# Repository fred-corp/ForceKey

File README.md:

# Force Key

## Description

The Force Key solid-state morse paddle key, which, as the name implies, uses force senors (load cells) to detect the user's input. It is designed to work in single-lever mode or twin-lever mode.  
The output is a standard 3.5mm stereo jack, which can be connected to any morse keyer or transceiver.

## Features

- Single-lever or twin-lever mode, or both at the same time
- Adjustable sensitivity in code
- TRS 3.5mm stereo jack output (tip = dot, ring = dash, sleeve = ground)
- Li-Ion battery powered
- USB-C port for charging
- Uses cheap Puya microcontroller

## Hardware

- PCB & other components in BOM
- 2x [100g load cells + HX711 amplifier](https://fr.aliexpress.com/item/1005001537354199.html) (make sure to get the 100g version !)
- TODO: add more details

The HX711 has to be modded to output data at 80Hz rate, which is done by lifting pin 15 and bridging it to pin 16 :  

## Inspiration

The Force key is inspired by the [Solid State Paddle by 9A5N](https://www.9a5n.eu/paddle.html), which is a beautiful product; but because of my student budget, I decided to make my own version.  
It was a nice challenge as I wanted to use the Puya PY32F002A microcontroller, which is not very common in the maker community.  
I also wanted to machine the base and load cell supports myself, which was exciting as I don't get to use the mills and lathes of my university very often as I'm an EE student.

Please consider buying the original product if you can afford it, it's a great product and it's worth the price (thanks [F4IEY](https://github.com/f4iey) for showing it to me in the first place !).

## Pictures

### 3D Render from Autodesk Fusion

### Base machining

The final base ended up being 90x85x20mm due to the available scrap blank; the CAD was then adapted to fit the new dimensions.

It was amazing to be able to use the machines of my university. It took a whole afternoon to machine both parts (base and load-cell support), but it was really fun ! Thanks again to my teacher for all the help and advice.

### Base bluing

Before :  

After :  

After a lot of sanding with 180 and 320 scotch-brite, I used a cold bluing solution to give the base a nice black finish. It's not perfect nor uniform, but it gives a great old-school look to the base.

### Assembly

Partial assembly before bluing :  

Assembly before bluing :  

Partial assembly after bluing :

Final assembly :

## License & Acknowledgements

Made with ❤️, lots of ☕️, and lack of 🛌  
Published under CreativeCommons BY-SA 4.0

This work is licensed under a [Creative Commons Attribution-ShareAlike 4.0 International License](http://creativecommons.org/licenses/by-sa/4.0/).

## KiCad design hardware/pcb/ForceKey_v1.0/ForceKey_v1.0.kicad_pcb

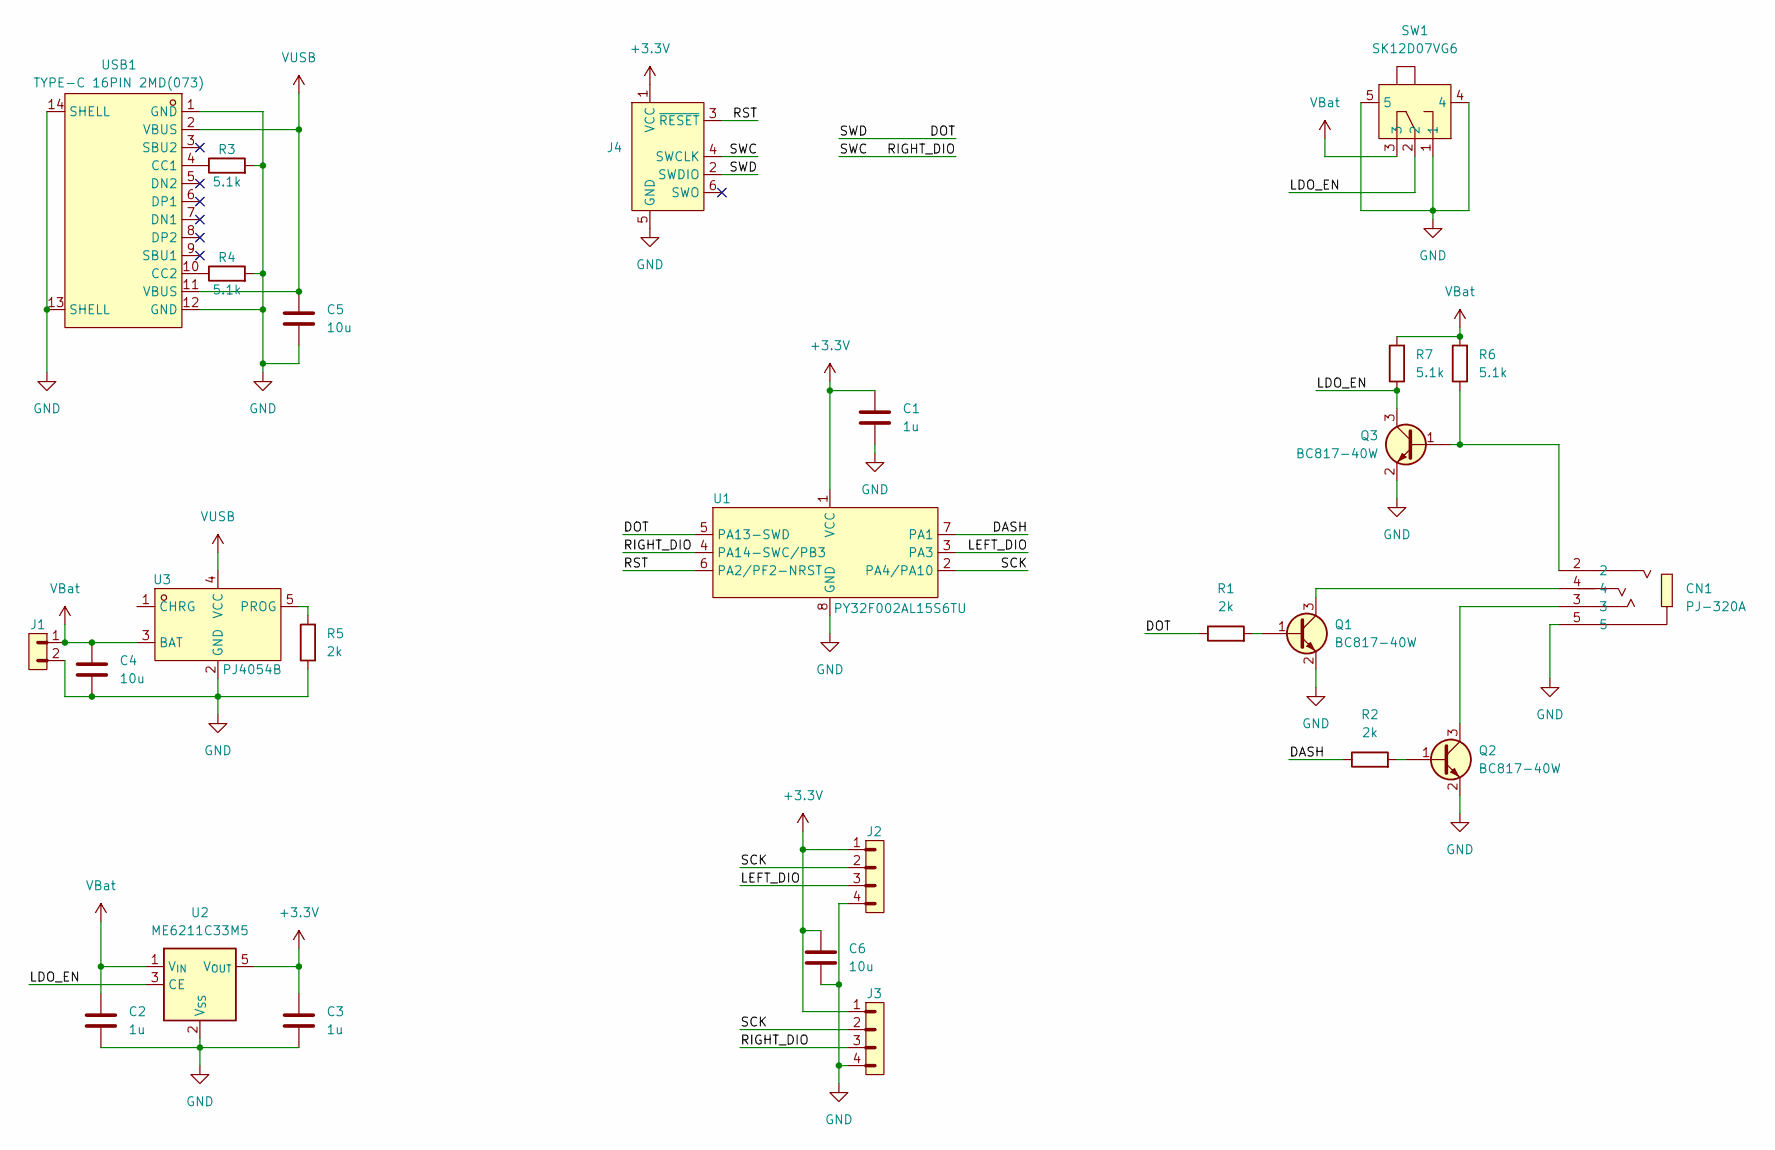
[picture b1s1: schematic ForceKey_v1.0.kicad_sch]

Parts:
C1, C2, C3: 1u; C_0603_1608Metric_Pad1.08x0.95mm_HandSolder
C4, C5, C6: 10u; C_0603_1608Metric_Pad1.08x0.95mm_HandSolder
CN1: PJ-320A; AUDIO-TH_XKB_PJ-320A; LCSC Part C2884926
J1: PINHD_1x2_Male; PinHeader_1x02_P2.54mm_Vertical
J2, J3: PINHD_1x4_Male; PinHeader_1x04_P2.54mm_Vertical
J4: Conn_ARM_SWD_TagConnect_TC2030-NL; Tag-Connect_TC2030-IDC-NL_2x03_P1.27mm_Vertical
Q1, Q2, Q3: BC817-40W; SOT-323_SC-70_Handsoldering
R1, R2, R5: 2k; R_0603_1608Metric_Pad0.98x0.95mm_HandSolder
R3, R4, R6, R7: 5.1k; R_0603_1608Metric_Pad0.98x0.95mm_HandSolder
SW1: SK12D07VG6; SW-TH_SK12D07VG6; LCSC Part C7272161
U1: PY32F002AL15S6TU; SOP-8_L4.9-W3.9-P1.27-LS6.0-BL-1; LCSC Part C5292060
U2: ME6211C33M5; SOT-23-5
U3: PJ4054B; SOT-23-5_L2.9-W1.6-P0.95-LS2.8-BL; LCSC Part C2911335
USB1: TYPE-C 16PIN 2MD(073); USB-C-SMD_TYPE-C-6PIN-2MD-073; LCSC Part C2765186

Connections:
+3.3V: C1.1, C3.1, C6.1, J2.1, J3.1, J4.1 (VCC), U1.1 (VCC), U2.5 (V_{OUT})
/DASH: R2.1, U1.7 (PA1)
/DOT: J4.2 (SWDIO), R1.1, U1.5 (PA13-SWD)
/LDO_EN: Q3.3 (C), R7.1, SW1.2, U2.3 (CE)
/LEFT_DIO: J2.3, U1.3 (PA3)
/RIGHT_DIO: J3.3, J4.4 (SWCLK), U1.4 (PA14-SWC/PB3)
/RST: J4.3 (~RESET), U1.6 (PA2/PF2-NRST)
/SCK: J2.2, J3.2, U1.2 (PA4/PA10)
GND: C1.2, C2.2, C3.2, C4.2, C5.2, C6.2, CN1.5, J1.2, J2.4, J3.4, J4.5 (GND), Q1.2 (E), Q2.2 (E), Q3.2 (E), R3.2, R4.2, R5.1, SW1.1, SW1.4, SW1.5, U1.8 (GND), U2.2 (V_{SS}), U3.2 (GND), USB1.1 (GND), USB1.12 (GND), USB1.13 (SHELL), USB1.14 (SHELL); also elsewhere on the board
unnamed: Q1.1 (B), R1.2
unnamed: CN1.4, Q1.3 (C)
unnamed: Q2.1 (B), R2.2
unnamed: CN1.3, Q2.3 (C)
unnamed: CN1.2, Q3.1 (B), R6.1
unnamed: R5.2, U3.5 (PROG)
unnamed: R3.1, USB1.4 (CC1)
unnamed: R4.1, USB1.10 (CC2)
VBat: C2.1, C4.1, J1.1, R6.2, R7.2, SW1.3, U2.1 (V_{IN}), U3.3 (BAT)
VUSB: C5.1, U3.4 (VCC), USB1.2 (VBUS), USB1.11 (VBUS)

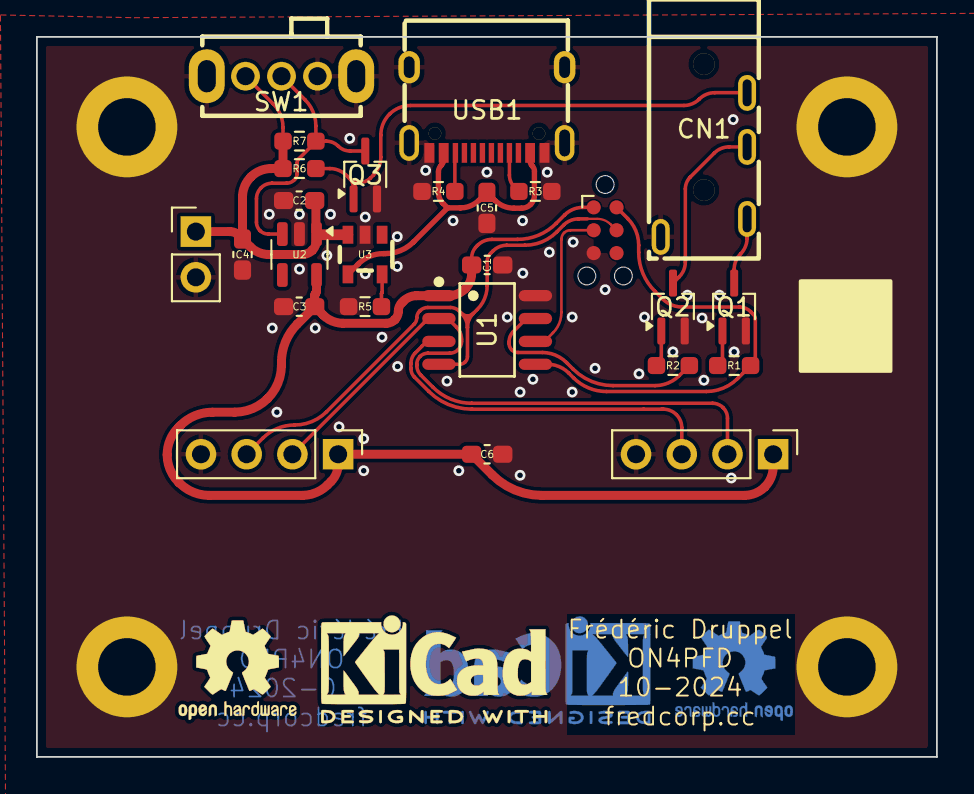
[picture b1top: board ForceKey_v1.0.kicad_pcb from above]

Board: 2 copper layers, 50.0 x 40.0 mm, 30 parts (0 on the bottom side), 19 nets.

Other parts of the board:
H1, H2, H3, H4: MountingHole_3.2mm_M3_DIN965_Pad

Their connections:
GND: H1.1, H2.1, H3.1, H4.1; also elsewhere on the board

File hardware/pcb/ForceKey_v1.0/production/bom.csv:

Designator,Footprint,Quantity,Value,LCSC Part #
"C1, C2, C3",0603,3,1u,
"C4, C5, C6",0603,3,10u,
CN1,AUDIO-TH_XKB_PJ-320A,1,PJ-320A,C2884926
J1,PinHeader_1x02_P2.54mm_Vertical,1,PINHD_1x2_Male,
"J2, J3",PinHeader_1x04_P2.54mm_Vertical,2,PINHD_1x4_Male,
"Q1, Q2, Q3",SOT-323_SC-70_Handsoldering,3,BC817-40W,
"R1, R2, R5",0603,3,2k,
"R3, R4, R6, R7",0603,4,5.1k,
SW1,SW-TH_SK12D07VG6,1,SK12D07VG6,C7272161
U1,SOP-8_L4.9-W3.9-P1.27-LS6.0-BL-1,1,PY32F002AL15S6TU,C5292060
U2,SOT-23-5,1,ME6211C33M5,
U3,SOT-23-5_L2.9-W1.6-P0.95-LS2.8-BL,1,PJ4054B,C2911335
USB1,USB-C-SMD_TYPE-C-6PIN-2MD-073,1,TYPE-C 16PIN 2MD(073),C2765186

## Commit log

2024-10-10 added trinity of Git repo files
2024-10-12 updated gitignore
2024-10-12 add initial KiCad files for ForceKey v1.0 including symbol and footprint libraries
2024-10-12 add template for PY32 dev environment
2024-10-14 added switch
2024-10-14 added switch & basic PCB layout draft
2024-10-14 added design rules
2024-10-14 added power traces, updated footprints
2024-10-26 used blink example for PY32F003x6
2024-10-26 updated PCB
2024-10-26 added report for ECAM machining shop
2024-10-26 converted main to CPP
2024-10-26 formatted files
2024-10-26 added HX711 read code
2024-10-27 added second HX711 handling
2024-10-27 fixed missing bracket
2024-10-27 fixed includes for IntelliSense
2024-10-27 added define parameters for pins
2024-10-27 added dot & dash pin handling
2024-10-28 fixed pin overlap with LED (dev), fixed variable names There was the CQWW contest, I didn't sleep much and coded between my shifts \^\^'
2024-10-28 uodated chip and pins
2024-10-28 moved files to dedicated folder
2024-10-28 Finished Schematic and PCB
2024-10-28 created fab files
2024-10-31 refactored code (never-nester strat), added options for single/double paddle
2024-10-31 updated J-Link command to reset target before erase Fixed "bricked" behavior of the PY32F002A chip even if nRST pin is not used as GPIO
2024-10-31 updated PCB settings
2024-11-01 added delay before setup, removed hack for j-link GPIO ini happens after delay, which solves the weird behaviors
2024-11-01 cleaned up code
2024-11-03 updated README with Force Key description, features, hardware details, and inspiration
2024-11-04 add timing waveform configuration in timing.wavedrom.json
2024-11-09 updated code to match PCB
2024-11-19 updated sensitivity (AGN)
2024-11-25 updated README with new images and additional details on HX711 modification and assembly process
2024-11-25 updated README to include Creative Commons license information
2024-11-25 fixed image link
2024-11-25 added funding
2025-01-01 updated toolchain location
2026-06-22 added schematic PDF
